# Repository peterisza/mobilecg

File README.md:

MobilECG II
===========

MobilECG II is an open source clinical grade Holter ECG. For more information, please visit http://mobilecg.hu.

NOTE: this is only a preliminary release. It contains known bugs, but its main structure will remain the same. There is no stable branch yet. Development occours on master. When a stable software is released, it will be split to separate stable and development branches.

Directory structure
-------------------
```
MobilECG II
├─  CAD - OpenSCAD drawings for the case and other parts
├─  Hardware - the hardware design of MobilECG II
│
├───Software
│    ├─  AndroidApp - Android demo application for resting ECG
│    ├─  Common - Source code used both in firmware and host app
│    └─  Firmware - Firmware running on the microcontroller
|
└───CardECG - Toy, credit card ECG project.

```

How to get one?
---------------

MobilECG is not publicly available yet. In order to sell a medical device, certification is needed. We are working hard to bring MobilECG to the users as soon as possible.

However you can still build one yourself. If you want to build it, feel free to do so. Contact us in case of any problems. There will be soon a technical blog where you will be able to find instructions on bulding one yourself.

Compatibility
-------------

The whole project is built using free or open source tools. The hardware is designed in KiCAD (http://kicad.org), the firmware compiles with ARM GCC (you can find binaries here: https://launchpad.net/gcc-arm-embedded), CAD files are designed with OpenSCAD (http://www.openscad.org) and 3D printed using MatterControl on a Prusa i3. The development occours on Mac OS X and Linux, building was never tested on Microsoft Windows (and we are not interested in making this software build on Windows except the Windows client app that will be written).

How to support us?
------------------

If you know a doctor or someone with a heart condition, please let them know about our project. Their subscription will help us find investment.

If you are a business angel or an investor, please contact us.

License
-------

The hardware is released under the Creative Commons Attribution-ShareAlike 4.0 International License. All software componens (except Bluetopia, STM32 peripherial libraries,
FreeRTOS, and scmRTOS, which are freely available) are licensed under the GNU Public License v3. If you have any special license requirements, please feel free to contact us.

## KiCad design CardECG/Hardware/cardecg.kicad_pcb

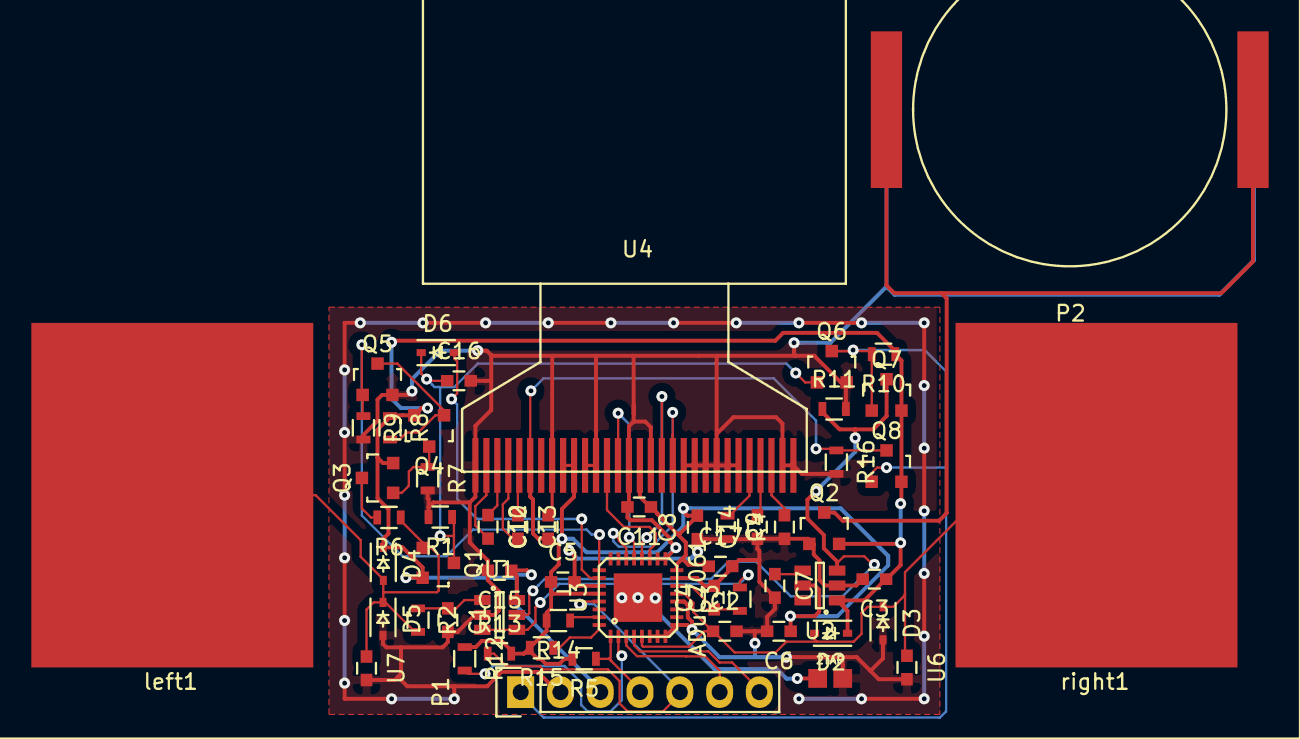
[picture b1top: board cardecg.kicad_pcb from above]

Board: 2 copper layers, 58 parts (0 on the bottom side), 38 nets.

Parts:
C1: 127pF; C_0603
C2: C; C_0603
C3, C6, C10, C11, C12, C13, C17: 1uF; C_0603
C4, C5, C8, C15, C16: 100nF; C_0603
C7: 10nF; C_0603
C9: 2.2uF; C_0603
C14: 4.7uF 16V; C_0603
CN1: 2TAP
D2, D3, D4, D5, D6: D; SOD-323
P1: PROG; Pin_Header_Straight_1x07
P2: BATTERY; CR2016
Q1, Q2, Q3, Q4, Q7, Q8: NTR1P02T1; SOT-23
Q5, Q6: NMOS_GSD; SOT-23
R1, R8, R9, R10, R11, R16: 100k; R_0603
R2, R5, R12, R13, R14, R15: 47k; R_0603
R3: 4k; R_0603
R4: 390k; R_0603
R6, R7: 20M; R_0603
U1: LMV341; SOT-23-6
U2: TPS717; SOT-23-6
U3: ADuC7061; LFCSP_VQ_CP32-2
U4: SSD1306
U5: creditcard
U6, U7: DNP; C_0603
left1: CONN_1; ecgpad
right1: CONN_1; ecgpad

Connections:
+BATT: C3.1, C15.1, D2.1, D4.1, P1.3, Q1.2, Q2.2, Q3.2, Q4.2, Q7.2, Q8.2, R8.1, R10.1, U1.6, U2.1
GND: C1.2, C2.2, C3.2, C4.2, C5.2, C6.2, C7.2, C8.1, C9.1, C10.2, C11.2, C14.1, C15.2, C16.2, C17.2, CN1.2, D3.2, D5.2, P1.2, P2.3, P2.4, Q2.1, Q5.2, Q6.2, R1.2, R4.2, R7.2, R9.2, R11.2, R16.2, U1.2, U2.2, U3.6, U3.7, U3.8, U3.9, U3.12, U3.15, U3.17, U3.18, U3.27, U4.1, U4.8, U4.11, U4.12, U4.15, U4.17, U4.20, U4.21, U4.22, U4.23, U4.24, U4.25, U4.29, U4.30, U6.2, U7.2
unnamed: C1.1, R2.1, U1.1
unnamed: C2.1, D2.2, D3.1, U3.5, U3.13, U6.1, right1.1
unnamed: C4.1, R3.1, U3.14
unnamed: C7.1, U2.4
unnamed: C9.2, U4.28
unnamed: C12.1, U4.3
unnamed: C12.2, U4.2
unnamed: C13.1, U4.5
unnamed: C13.2, U4.4
unnamed: C14.2, U4.27
unnamed: C16.1, D6.1, Q1.3, Q6.1, R1.1
unnamed: CN1.1, U3.33
unnamed: D4.2, D5.1, Q1.1, R2.2, R6.1, U7.1, left1.1
unnamed: P2.1, P2.2, Q2.3
unnamed: Q3.1, Q4.3, R7.1
unnamed: Q3.3, R6.2
unnamed: Q4.1, Q5.3, R8.2
unnamed: R3.2, U1.3, U1.4
unnamed: R4.1, U4.26
unnamed: R12.2, U3.2
unnamed: R14.1, U3.31
unnamed: R15.1, U3.32
unnamed: U3.19, U4.13
unnamed: U3.20, U4.18
unnamed: U3.21, U4.14
unnamed: U3.22, U4.19
OLED_PWR: C10.1, Q8.3, R16.1, U4.6
POWER_ON: D6.2, U3.26
PULLUP_OFF: Q5.1, R9.1, U3.25
RX: P1.6, U3.3
TX: P1.7, U3.4
VCC: Q7.3, R11.1, U1.5, U2.3
VDD: C5.1, C6.1, C8.2, C11.1, C17.1, R5.2, R12.1, R13.2, R14.2, R15.2, U2.5, U3.16, U3.28, U4.9, U4.10, U4.16
~FORCE_ON: P1.1, Q6.3, Q7.1, Q8.1, R10.2
~PROG: P1.5, R13.1, U3.29
~RESET: P1.4, R5.1, U3.1

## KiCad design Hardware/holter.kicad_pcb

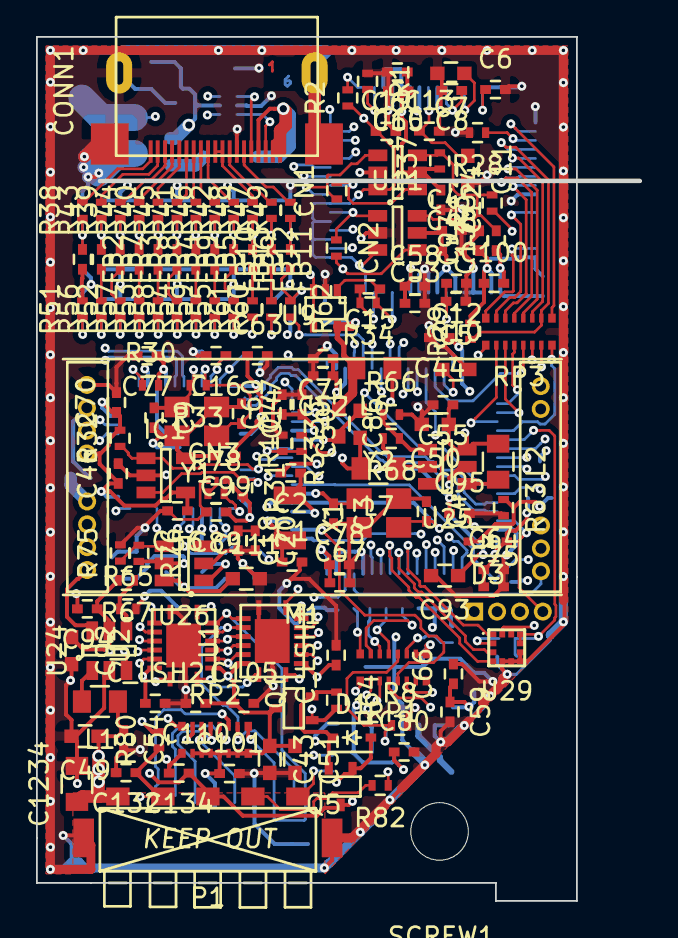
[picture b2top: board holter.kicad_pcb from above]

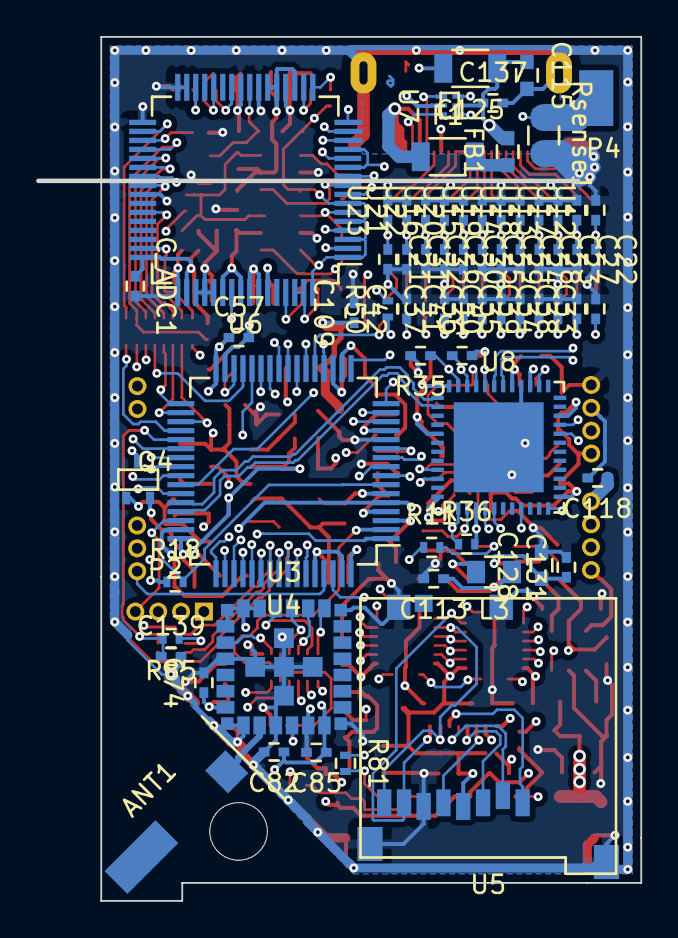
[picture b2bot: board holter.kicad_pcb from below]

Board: 6 copper layers, 30.0 x 48.0 mm, 231 parts (70 on the bottom side), 176 nets.

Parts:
ANT1: 2450AT42A100
C1, C2: 6pF; C_0402
C3, C4: C_Small; C_0402
C5: 4.7uF LOW ESR; C_0603
C6, C8, C10, C16, C18, C44, C45, C52, C53, C59, C60, C61, C67, C75, C80, C97: 1uF; C_0402
C7, C51: 22uF; C_0603
C9, C14: 33pF; C_0402
C11, C43, C49, C50, C86, C92, C93, C111, C128, C501: 10uF; C_0603
C12, C13, C17, C20, C46, C47, C48, C54, C55, C56, C57, C58, C63, C64, C65, C66, C70, C71, C77, C78, C82, C89, C94, C95, C99, C100, C101, C105, C109, C110, C113, C118, C124, C131, C134, C135, C137, C139: 100nF; C_0402
C15: 10nF; C_0402
C19, C74, C85: 100pF; C_0402
C21, C22, C23, C24, C25, C26, C27, C28, C29, C30, C31, C32, C33, C34, C35, C36, C37, C38, C39, C40, C41, C42: 47pF; C_0402
C115: 10uF 10V; C_0603
C125: 47uF; C_1206
C132: 100n; C_0402
C1234: 22uF; C_0805
CN1, CN2: 2TAP; R_0402
CN3: 3TAP; SOLDERJUMPER3
CONN1: HDMI; 2013978
C_ADC1: 100nF; C_0402
C_LSH1, C_LSH2: 100nF; C_0402
D1, D3: DB2S20500L; SOD-323
F1: 1206L075THYR; C_1206
FB1: MPZ1608D101B (100Ohm @ 100MHz, 1A, 0603); C_0603
FB2, FB3, FB4, FB5, FB6, FB7, FB8, FB9, FB10, FB11, FB12, FB13: FILTER; C_0402
IC1: 256kx8; SOT-23-5
L1, L2, L3: 4.7uH PFL2015-472MEC; C_0805
L6, L7: 4.7uH; C_0805
M1: USB_Power_Module; USB_POWER_MODULE
P1: CONN_01X07; MOBO9155
P2: PROG; HEADER127_4
P4: BAT-; S7121-42R
Q1, Q4, Q5: PMF170XP; SC-70
R1, R2: 1k; R_0402
R8, R11, R28, R36, R37, R50, R63, R64, R80, R85: 100k; R_0402
R10, R65, R66, R67, R68, R75, R76, R81, R82, R3333: R; R_0402
R18, R29, R30, R31, R32, R51, R52, R53, R54, R55, R56, R57, R58, R59, R60, R83: 10k; R_0402
R33: 1M; R_0402
R34: 392k; R_0402
R35: 12k 1%; C_0402
R38, R39, R40, R41, R42, R43, R44, R45, R46, R47, R48, R49, R61: 470; R_0402
R62: 47k; R_0402
R78: 100; R_0402
RP1, RP3: 51R EXB2HV510JV; EXB2HV
RP2: 100k EXB2HV104JV; EXB2HV
Rsense1: 0.1 1%; C_0805
SCREW1: SCREW; M3_SCREW
U1, U2: TXB0106; RGY16
U3: TiWi-uB2; TIWIUB2
U4: STM32F4x1_64; TQFP-64_10x10mm_Pitch0.5mm
U5: uSD; MEM2051
U6: ADS1298; TQFP-64_10x10mm_Pitch0.5mm
U7: USBULC6-2M6; USBULC62M6
U8: USB2641; QFN-48-1EP_7x7mm_Pitch0.5mm
U9: OPA379; SC-70-5
U10, U11: TS5A3159; SOT-23-6
U12, U13, U14, U15, U16, U17, U18, U19, U20, U21, U22, U23: ESD_PROTECTOR; C_0402
U24, U25, U26: TLV61220; SOT-23-6
U29: LIS2DH12; LGA12
X1: 32768; FC135
Y1: 24 MHz; TSX3225
Y2: 10 MHz; TSX3225

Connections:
32768_CLK: RP1.6, U4.41
+1V8: C80.1, C82.1, C85.1, C97.1, C100.1, C501.1, C_ADC1.1, C_LSH1.1, L7.2, Q4.3, R29.2, R50.1, R80.2, U1.2, U3.18, U6.48, U6.50
+2.8VA: C45.1, C48.1, C53.1, C58.1, C61.1, C65.1, C86.1, C109.1, C124.1, L6.2, R37.1, U6.19, U6.21, U6.22, U6.54, U6.56, U6.59, U9.5, U10.5, U11.5
+2.8VD: C59.1, C66.1, C74.1, C92.1, C94.1, C134.1, M1.12, P1.3, Q5.3, R67.2, U3.12, U24.5
+3V3: C46.1, C56.1, C63.1, C70.1, C77.1, C89.1, C99.1, CN3.1, C_LSH2.1, D1.2, D3.2, IC1.4, M1.4, Q4.1, Q5.1, R30.2, R31.2, R32.2, R36.2, R63.1, U2.15, U8.5, U8.12, U8.16, U8.25, U8.34, U8.41, U8.48
+5V: C115.1, C118.1, C125.1, C137.1, FB1.2, M1.5, M1.6, U4.42, U7.5, U8.39
ACC_CLK: U4.55, U29.1
ACC_CS: R85.1, U4.50, U29.2
ACC_INT: U4.38, U29.12
ACC_MISO: U4.56, U29.3
ACC_MOSI: U4.57, U29.4
ACC_PWR: C139.1, R85.2, U4.37, U29.9, U29.10
ADCLK: RP3.6, U4.43
BAT+: C49.1, C50.1, C54.1, C55.1, C111.1, C113.1, C1234.1, L1.1, L2.1, L3.1, M1.7, M1.8, P1.1, R10.2, U24.6, U25.3, U25.6, U26.6
BTN: C132.1, P1.2, R80.1, U4.62
CABLE_DETECT: R62.2, U4.21
CR_CLK: U2.16, U8.21
CR_CMD: U2.14, U8.24
CR_D0: U2.10, U8.18
CR_D1: U2.11, U8.17
CR_D2: U2.12, U8.33
CR_D3: U2.13, U8.32
CR_SEL: RP2.7, U2.8, U4.27
CTS: RP1.2, U4.14
D+: U7.6, U8.42
D-: U7.4, U8.43
DETECT: CONN1.14, R49.2
DIFF_SEL: R83.1, U4.24
ECG_START: RP3.5, U4.29
EN_2V8: R11.2, U24.3, U26.3
EN_3V3: M1.13, U4.61
GND: C1.2, C2.2, C3.2, C4.1, C5.2, C6.2, C7.2, C8.2, C9.2, C10.1, C11.2, C12.1, C13.2, C14.1, C16.2, C17.2, C18.2, C19.2, C20.2, C21.2, C22.2, C23.2, C24.2, C25.2, C26.2, C27.2, C28.2, C29.2, C30.2, C31.2, C32.2, C33.2, C34.2, C35.2, C36.2, C37.2, C38.2, C39.2, C40.2, C41.2, C42.2, C43.2, C44.2, C45.2, C46.2, C47.2, C48.2, C49.2, C50.2, C51.2, C52.2, C53.2, C54.2, C55.2, C56.2, C57.2, C58.2, C59.2, C60.2, C61.2, C63.2, C64.2, C65.2, C66.2, C67.2, C70.2, C71.2, C74.2, C75.2, C77.2, C78.2, C80.2, C82.2, C85.2, C86.2, C89.2, C92.2, C93.2, C94.2, C95.2, C97.2, C99.2, C100.2, C101.2, C105.2, C109.2, C110.2, C111.2, C113.2, C115.2, C118.2, C124.2, C125.2, C128.2, C131.2, C132.2, C134.2, C135.1, C137.2, C139.2, C501.2, C1234.2, CN3.3, CONN1.13, CONN1.20, CONN1.21, CONN1.22, CONN1.23, C_ADC1.2, C_LSH1.2, C_LSH2.2, IC1.2, IC1.5, M1.1, M1.2, P1.6, P1.7, P2.3, R1.1, R8.2, R28.2, R35.2, R63.2, R65.2, R66.2, R75.2, R3333.1, RP1.9, RP1.10, RP2.9, Rsense1.2, U1.9, U1.17, U2.9, U2.17, U3.5, U3.6, U3.7, U3.9, U3.13, U3.15, U3.17, U3.25, U3.26, U3.27, U3.28, U3.29, U3.30, U3.31, U3.32, U3.33, U4.12, U4.18, U4.31, U4.47, U4.60, U4.63, U5.6, U5.9, U5.10, U5.11, U5.12, U6.20, U6.23, U6.25, U6.31, U6.32, U6.33, U6.41, U6.49, U6.51, U6.52, U6.53, U6.57, U6.58, U7.2, U8.40, U8.49, U9.2, U10.2, U11.2, U12.2, U13.2, U14.2, U15.2, U16.2, U17.2, U18.2, U19.2, U20.2, U21.2, U22.2, U23.2, U24.2, U25.2, U26.2, U29.5, U29.6, U29.7, U29.8, Y1.2, Y1.4, Y2.2, Y2.4
G_PWM: R82.1, U4.59
LA: CONN1.6, R45.2
LA_F: C40.1, R58.1, U6.14
LL: CONN1.8, R46.2
LL_F: C41.1, R59.1, U6.12
MCU_USB_D+: U4.45, U8.2
MCU_USB_D-: U4.44, U8.1
unnamed: ANT1.1, U3.14
unnamed: C1.1, U4.3, X1.1
unnamed: C2.1, U4.4, X1.2
unnamed: C3.1, U4.6, Y2.3
unnamed: C4.2, U4.5, Y2.1
unnamed: C5.1, U4.30
unnamed: C6.1, U6.30
unnamed: C7.1, U6.28
unnamed: C8.1, U6.26
unnamed: C9.1, R33.2, U8.44, Y1.1
unnamed: C10.2, C12.2, U6.55
unnamed: C11.1, C13.1, U6.24
unnamed: C14.2, R33.1, U8.45, Y1.3
unnamed: C15.1, R34.1, U6.61, U9.1
unnamed: C16.1, C17.1, U8.46
unnamed: C18.1, C20.1, U8.15
unnamed: C19.1, R2.1, U6.1, U6.3, U6.5, U6.7, U6.64, U10.3, U11.3
unnamed: C21.1, FB13.2, R49.1, U23.1
unnamed: C22.1, FB2.1, R38.1, U12.1
unnamed: C23.1, FB3.1, R39.1, U13.1
unnamed: C24.1, FB4.1, R40.1, U14.1
unnamed: C25.1, FB5.1, R41.1, U15.1
unnamed: C26.1, FB6.1, R42.1, U16.1
unnamed: C27.1, FB7.1, R43.1, U17.1
unnamed: C28.1, FB8.1, R44.1, U18.1
unnamed: C29.1, FB9.1, R45.1, U19.1
unnamed: C30.1, FB10.1, R46.1, U20.1
unnamed: C31.1, FB11.1, R47.1, U21.1
unnamed: C32.1, FB12.1, R48.1, U22.1
unnamed: C93.1, C95.1, L7.1, R68.2, U25.5
unnamed: C128.1, C131.1, L6.1, R76.2, U26.5
unnamed: C135.2, R37.2, R83.2, U10.6, U11.6
unnamed: CN1.2, U6.9, U10.4
unnamed: CN2.2, U6.15, U11.4
unnamed: CN3.2, R78.1
unnamed: CONN1.15, U7.1
unnamed: CONN1.16, CONN1.18, CONN1.19, F1.1
unnamed: CONN1.17, U7.3
unnamed: D1.1, Q1.2, Q5.2, R64.1
unnamed: F1.2, FB1.1
unnamed: FB2.2, R51.2
unnamed: FB3.2, R52.2
unnamed: FB4.2, R53.2
unnamed: FB5.2, R54.2
unnamed: FB6.2, R55.2
unnamed: FB7.2, R56.2
unnamed: FB8.2, R57.2
unnamed: FB9.2, R58.2
unnamed: FB10.2, R59.2
unnamed: FB11.2, R60.2
unnamed: FB12.2, R61.2
unnamed: FB13.1, R50.2, R62.1
unnamed: IC1.1, R32.1, U8.9
unnamed: IC1.3, R31.1, U8.10
unnamed: L1.2, U24.1
unnamed: L2.2, U25.1
unnamed: L3.2, U26.1
unnamed: M1.3, P4.1, Rsense1.1
unnamed: P1.4, R82.2
unnamed: P1.5, R81.2
unnamed: R1.2, U6.18
unnamed: R2.2, U6.17
unnamed: R8.1, RP1.12, U3.16
unnamed: R10.1, R3333.2, U4.11
unnamed: R11.1, U4.9
unnamed: R29.1, RP3.10, U6.36
unnamed: R30.1, U8.38
unnamed: R35.1, U8.47
unnamed: R65.1, R67.1, U24.4
unnamed: R66.1, R68.1, U25.4
unnamed: R75.1, R76.1, U26.4
unnamed: R78.2, U8.13
unnamed: RP1.11, U3.8
unnamed: RP1.13, U3.3
unnamed: RP1.14, U3.2
unnamed: RP1.15, U3.4
unnamed: RP1.16, U3.1
unnamed: RP2.1, U1.10, U2.7, U5.7
unnamed: RP2.2, U1.11, U2.6, U5.8
unnamed: RP2.3, U1.12, U2.5, U5.1
unnamed: RP2.4, U1.13, U2.4, U5.2
unnamed: RP2.5, U1.14, U2.3, U5.3
unnamed: RP2.6, U1.16, U2.1, U5.5
unnamed: RP3.9, U6.34
unnamed: RP3.11, U6.37
unnamed: RP3.12, U6.38
unnamed: RP3.13, U6.39
unnamed: RP3.14, U6.40
unnamed: RP3.15, U6.43
unnamed: RP3.16, U6.47
RA: CONN1.4, R44.2
RA_F: C39.1, R57.1, U6.11, U6.13
RLD: CONN1.12, R47.2
RLD_UF: C15.2, C42.1, R34.2, R60.1, U6.62, U6.63
RTS: RP1.1, U4.15
RX: RP1.3, U4.17
R_PWM: R81.1, U4.58
SDIO_CLK: U1.1, U4.53
SDIO_CMD: U1.3, U4.54
SDIO_D0: U1.7, U4.39
SDIO_D1: U1.6, U4.40
SDIO_D2: U1.5, U4.51
SDIO_D3: U1.4, U4.52
SD_CPU: RP2.8, U1.8, U4.28
SHIELD: CONN1.10, CONN1.11, R48.2
SHIELD_UF: R61.1, U9.3, U9.4
SPI_MISO: RP3.2, U4.35
SPI_MOSI: RP3.8, U4.36
SPI_SCK: RP3.3, U4.34
SWCLK: P2.1, U4.49
SWDIO: P2.4, U4.46
TX: RP1.4, U4.16
V1: CONN1.1, R38.2
V1_F: C33.1, R51.1, U6.2
V2: CONN1.3, R39.2
V2_F: C34.1, R52.1, U6.10
V3: CONN1.5, R40.2
V3_F: C35.1, CN1.1, R53.1, U6.8, U10.1
V4: CONN1.7, R41.2
V4_F: C36.1, CN2.1, R54.1, U6.6, U11.1
V5: CONN1.9, R42.2
V5_F: C37.1, R55.1, U6.4
V6: CONN1.2, R43.2
V6_F: C38.1, R56.1, U6.16
VBAT: M1.11, U4.1
VCPU: C44.1, C47.1, C52.1, C57.1, C60.1, C64.1, C67.1, C71.1, C75.1, C78.1, D3.1, Q4.2, R18.1, U4.13, U4.19, U4.32, U4.48, U4.64
VMEM: C43.1, C51.1, C101.1, C105.1, C110.1, Q1.3, RP2.10, RP2.11, RP2.12, RP2.13, RP2.14, RP2.15, RP2.16, U1.15, U2.2, U5.4
~BT_SHDN: RP1.5, U4.2
~CARD_DET: R36.1, U4.10, U8.14
~CHRG_EN: M1.10, U4.26
~CHRG_STAT: M1.9, U4.25
~ECG_CS: RP3.4, U4.33
~ECG_DRDY: RP3.1, U4.20
~ECG_PWDN: R28.1, U4.23, U6.35
~ECG_RST: RP3.7, U4.22
~RST: P2.2, R18.2, U4.7
~SD_EN: Q1.1, R64.2, U4.8

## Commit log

2014-09-14 Initial commit.
2014-09-14 Fix typoos
2014-09-17 Fix even more typos, arrange parts in the schematic.
2014-09-17 Remove missing library.
2014-10-04 Accelerometer. Not connected yet.
2014-10-05 Accelerometer connected.
2014-10-05 Invert switch edge polarity for easier PCB routing.
2015-02-19 Make project compatible with new kicad.
2015-09-27 Modified schematic to load properly with new KiCAD
2015-10-05 Remove wire part outside the schematic page added.
2015-10-06 Power switching optimizations
2015-10-06 Charger short circuit fix. Capacitor optimizations.
2015-10-06 Reverse diode fix. Cap changes.
2015-10-07 Footprints, LC filter
2015-10-07 Reorder RC cap. Remove holter-rescue library.
2015-10-07 More footprints.
2015-10-07 Remove EEPROM programming port
2015-10-07 Enclosure initial commit.
2015-10-07 Resistor nets + HTQFP_64 footprint.
2015-10-08 Rearrangement.
2015-10-08 Fixed ADS1298 library.
2015-10-09 MicroSD connector pdf, Level shifter QFN -> TSSOP
2015-10-11 More footprints
2015-10-12 Footprints...
2015-10-12 Footprints.
2015-10-15 Prog header
2015-10-15 Led flashing. Build system. Fixed loader.
2015-10-16 New, surface mounted HDMI connector
2015-10-17 Outline drawings.
2015-10-17 Placement...
2015-10-18 spi lib
2015-10-18 Display working
2015-10-19 New HDMI Type-C footprint, BOM
2015-10-19 Grounding point, LC filter at 1.8V supply
2015-10-19 Fast display IO.
2015-10-20 PCB mounting
2015-10-20 Placement of the I/O filtering components
2015-10-20 Component placement + add 3.3V enable pin
2015-10-20 Component groups
2015-10-21 USB charger and power supply is now a separate module
2015-10-23 Text rendering
2015-10-23 UART
2015-10-23 printf
2015-10-23 Make font constant
2015-10-23 Logo converter
2015-10-23 multiline text rendering
2015-10-23 Make logo image const.
2015-10-23 Placement of parts.
2015-10-24 Placement + additional bypass capacitors.
2015-10-24 Removed unnecessary bypass capacitors.
2015-10-24 Reduce stack sizes.
2015-10-24 Initial ADC code
2015-10-24 I/O filter connections on PCB.
2015-10-25 Fixed ADS1298 footprint. Routing of the analog parts.
2015-10-25 Connected ECG signals to the AD.
2015-10-25 Routing attempt.
2015-10-26 Fix QFN48 footprint. Another routing attempt.
2015-10-26 Moved the card reader to the other side. More routes.
2015-10-26 ECG working
2015-10-27 More traces.
2015-10-27 Random modifications
2015-10-27 Performance improvements. Backward filtering.
2015-10-28 Rearrangement of CPU pins, even more traces, fixed LGA footprint
2015-10-28 Pin rearrangement, more traces.
2015-10-28 More PCB traces.
2015-10-28 Everything is connected on the main board.
2015-10-29 New footprint for the inductor of the charger.
2015-10-30 Main board differential pairs + screw.
2015-11-07 coil datasheet.
2015-11-07 New gitignore for CardECG
2015-11-07 CardECG initial commit
2015-11-07 Fix gitignore
2015-11-07 Fix programming port. Connect unused analog inputs to GND. Add required pullups to JTAG.
2015-11-07 Some cosmetic improvements. Make room for the matic transistor input switch.
2015-11-07 Magic power switch
2015-11-07 Connect the magic switch, fix ERC, some cosmetics.
2015-11-07 Cosmetics
2015-11-07 Changed input fet to low capacitance one.
2015-11-07 Opamp type added.
2015-11-07 More gnds.
2015-11-07 ESD protectors + force on connector
2015-11-07 1uF cap on agnd
2015-11-08 Additional pins on programming port
2015-11-08 new gitignore
2015-11-08 New PCB
2015-11-08 Added filter cap for the first switch transistor
2015-11-08 Added gerber files
2015-11-08 Moved the components a little bit upward.
2015-11-08 Added 1uF capacitor to AVDD
2015-11-08 forgot to save
2015-11-08 Changed title
2015-11-09 QRS detector
2015-11-11 Finished PCB with 6 mil traces, removed module components.
2015-11-18 New enclosure design in OpenSCAD.
2015-11-18 Connector slot.
2015-11-20 Enclosure lid rails.
2015-11-20 Remove text from logo.svg.
2015-11-21 Lid initial commit.
2015-11-21 Fix r.h.s. hook on lid.
2015-11-21 Increased cylinder resolution.
2015-11-27 New power supply support
2015-12-04 Fix back wall width, remove unnecessary plastic.
2015-12-05 Gitignore for firmware
2015-12-05 Initial firmware commit. Not compiling yet
2015-12-05 Add rejected patch files to gitignore
2015-12-05 Fix hardware initialization code.
2015-12-05 Compiling, but not linking.
2015-12-05 Various fixes. Not linking yet.
2015-12-05 Fix SystemCoreClock missing
2015-12-05 Add missing _sbrk()
2015-12-05 Fix typo, add values to scheamtic.
2015-12-05 Declare static variables to fix the build.
2015-12-07 Eclipse project.
2015-12-09 DataFormat library, initial commit.
2015-12-09 Plastic part for the card ecg.
2015-12-09 Card ECG sticker.
2015-12-10 Fix PCB rail at the back
2015-12-12 Signal quality measurement, automatic power off.
2015-12-12 startup works, OS not.
2015-12-13 Move to FreeRTOS
2015-12-13 leds flashing.
2015-12-13 szar az egész.
2015-12-14 bluetooth compiling.
2015-12-18 Fix turn off bug.
2015-12-21 Bluetooth init, not working yet
2015-12-21 bluetooth module communication working.
2015-12-21 Trying to make this piece of shit discoverable without success.
2015-12-22 Fix Bluetopia Patch. Remove some redundant functions.
2015-12-22 pairing works.
2015-12-23 Gave data format classes better names.
2015-12-23 Bluetooth write. Doesn't works.
2015-12-23 Fix the big endian integer class and the serializer test.
2015-12-23 Add *.o to .gitignore.
2015-12-23 Remove mistakenly committed object files.
2015-12-27 Use libc malloc in FreeRTOS. Fix _sbrk() to handle heap boundaries properly.
2015-12-29 Battery power supply guide
2015-12-30 CPU controls 2.8V supply. Add inversion support for GPIO class. Increase BT baud rate.
2015-12-31 Fix hanging on send.
2015-12-31 Prevent copy when reading from circular buffer.
2016-01-04 Fix bluetooth send deadlock.
2016-01-04 ECG clock generation.
2016-01-05 Modified config for ECG SPI interface. Hacked make patch to "fix" the issue with patch trying to patch the original file instead the modified one.
2016-01-05 ADS1298 GPIO definitions.
2016-01-06 ADS1298 register access code. Not working yet.
2016-01-07 ADS1298 startup code working. EXTI interrupt handler added.
2016-01-11 12 lead cable prototype
2016-01-12 Enclosure enhancements.
2016-01-12 Ecg data transfer working.
2016-01-12 Fix PCB rail again.
2016-01-12 Remove test cutting cube.
2016-01-12 Fix the distance between i and l again.
2016-01-13 Prototype written on the front side too.
2016-01-13 Fix sampling frequency.
2016-01-13 Send ECG. Not working.
2016-01-13 Fix sending.
2016-01-13 Fix circular buffer. Increase BT buffer size.
2016-01-14 Handle error codes in bluetooth send.
2016-01-15 ECG compression initial commit.
2016-01-17 Ecg compression now working.
2016-01-17 Make it possible to fill BT fifo without begininng a new transmission. Stream packetizer.
2016-01-17 First try for sending packetized ECG. BT is singleton now.
2016-01-17 Sending seems to work.
2016-01-17 Add common ECG code to firmware. Fix infinite number of warnings.
2016-01-17 Sending ECG compressed. Not working yet. Modified ECG compressor interface to be more suitable for embedded environment.
2016-01-20 Compressed ECG sending works.
2016-01-21 Android app initial commit.
2016-01-21 Grid works.
2016-01-22 DPI working.
2016-01-22 Send vertex buffer only once. Fix grid drawer last line. Fix DPI settings.
2016-01-22 Remove android studio .idea files and add them to gitignore.
2016-01-23 Bluetooth thread.
2016-01-23 Scramble shit.
2016-01-23 Fix return value of ECG compressor functions.
2016-01-23 Move packetizer to common place.
2016-01-23 Move circular buffer to common code. Add common code to android app.
2016-01-23 Header checksum.
2016-01-23 Invert chechsum signs.
2016-01-23 Fix circular buffer bug.
2016-01-23 PacketReader initial commit.
2016-01-24 Curve drawer initial commit.
2016-01-24 Packet reader with test.
2016-01-24 First ECG test.
2016-01-24 Packets received.
2016-01-26 Test signal generator.
2016-01-26 Fixed the compression and the decompression.
2016-01-26 ECG test sender.
2016-01-26 Fast sine.
2016-01-26 Fast sine again.
2016-01-26 Rename test signal generator.
2016-01-26 Sawtooth signal generator
2016-01-26 Fix everything.
2016-01-27 Fix everythig again.
2016-01-27 An attempt to fix the circular buffer.
2016-01-27 Notch filter initial commit.
2016-01-27 Removed the acceleration sensor curve, added the notch filter to the app.
2016-01-27 Drawing after resuming the application works.
2016-01-27 Some ADS1298 registers.
2016-01-27 ECG layout and scaling.
2016-01-27 Remove overwrite from circular buffer.
2016-01-27 Remove full flag from circular buffer.
2016-01-28 Increase CPU speed.
2016-01-28 Idle task.
2016-01-29 Fix FreeRTOS tasks.c to enable link time optimizations and remove warning.
2016-01-29 Faster and more elegant endian change. Sign exension before compression. ECG compressor hardcoded to int32_t (sizeof(int)==random)
2016-01-29 Enable Wilson's Central Terminal.
2016-01-31 Fix curve buffer size.
2016-02-01 Remove mutex for bluetooth circular buffer in a thread-safe way. This seems to fix the disconnect hangup issue.
2016-02-01 Fix O2 startup bug.
2016-02-02 SPI O2 bug fixed? Reduce sample bit size. Switchable debugs. Increase send block size.
2016-02-03 Avoid building multiple GLPrograms for the instances of the same shader.
2016-02-04 New baseline filter and notch filter.
2016-02-04 Working on the bidirectional ECG filter.
2016-02-04 Fix compilation bugs in previous commit.
2016-02-04 Fix bidirectional filtering.
2016-02-04 Removed file symlinks, added directory symlinks. Forward baseline filtering is now active. Initial commit of TextDrawer.
2016-02-04 Remove binary.
2016-02-04 Fix .gitignore for Tests/.
2016-02-04 Reset ShaderBuilder when OpenGL surface is recreated.
2016-02-04 Circle on the end of the curve. Preven unnecessary glUseProgram() calls. Remove unused parts of textureSurface.vert. Prevent resizing curve buffer to 0.
2016-02-05 The text renderer is now called from C++ via JNI.
2016-02-05 ECG channel labels.
2016-02-05 Better label placing, development version notice.
2016-02-05 Hide navbar.
2016-02-05 Fix filter. Better navbar hiding.
2016-02-05 Fix "DEVELOPMENT VERSION" label position.
2016-02-05 Calculation of the standard 12 leads.
2016-02-05 Add git version to "DEVELOPMENT VERSION" label.
2016-02-05 Store link keys in circular manner. Increase link key storage size.
2016-02-05 Better(?) notch filter.
2016-02-05 App renamed.
2016-02-05 Filter changed.
2016-02-05 Icon.
2016-02-06 Fixed curve startup.
2016-02-06 Fix the gain of everything.
2016-02-06 Better ECG layout.
2016-02-07 Keeo screen on.
2016-02-07 Better filter
2016-02-07 Another baseline filter.
2016-02-07 EEPROM emulation in flash. Store link keys in eeprom.
2016-02-07 Disconnected label/reconnect button.
2016-02-07 Scanning + BT linkkey change fix.
2016-02-07 Long click opens menu. Scan automatically opens when no paired device is available.
2016-02-08 Fix baseline filter.
2016-02-09 Schematic fixes.
2016-02-13 Reorganize folder structure
2016-02-13 Fix symlinks broken because reorganization.
2016-02-13 Further repo cleaning.
2016-02-13 Minor cleanups.
2016-02-13 Add license agreement.
2016-02-14 Readme and schematic changes.
2016-02-14 More readme.md.
2016-02-14 README.md edited online with Bitbucket
2016-02-15 Hardware License
2016-02-15 CAD/ is also licensed under CC-SA-4.0
2016-02-15 License updates.
2016-02-16 License update.
2016-02-20 Fix CardECG power feedback from display.
2021-11-08 Update README.md
    https://forum.kicad.info/t/warning-avoid-all-links-to-kicad-pcb-org-use-kicad-org/31521

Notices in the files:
Hardware/holter.kicad_pcb:
Licensed under Creative Commons Attribution-ShareAlike 4.0 International License
The mobilECG hardware by Peter Isza & Robert Csordas is licensed under a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
